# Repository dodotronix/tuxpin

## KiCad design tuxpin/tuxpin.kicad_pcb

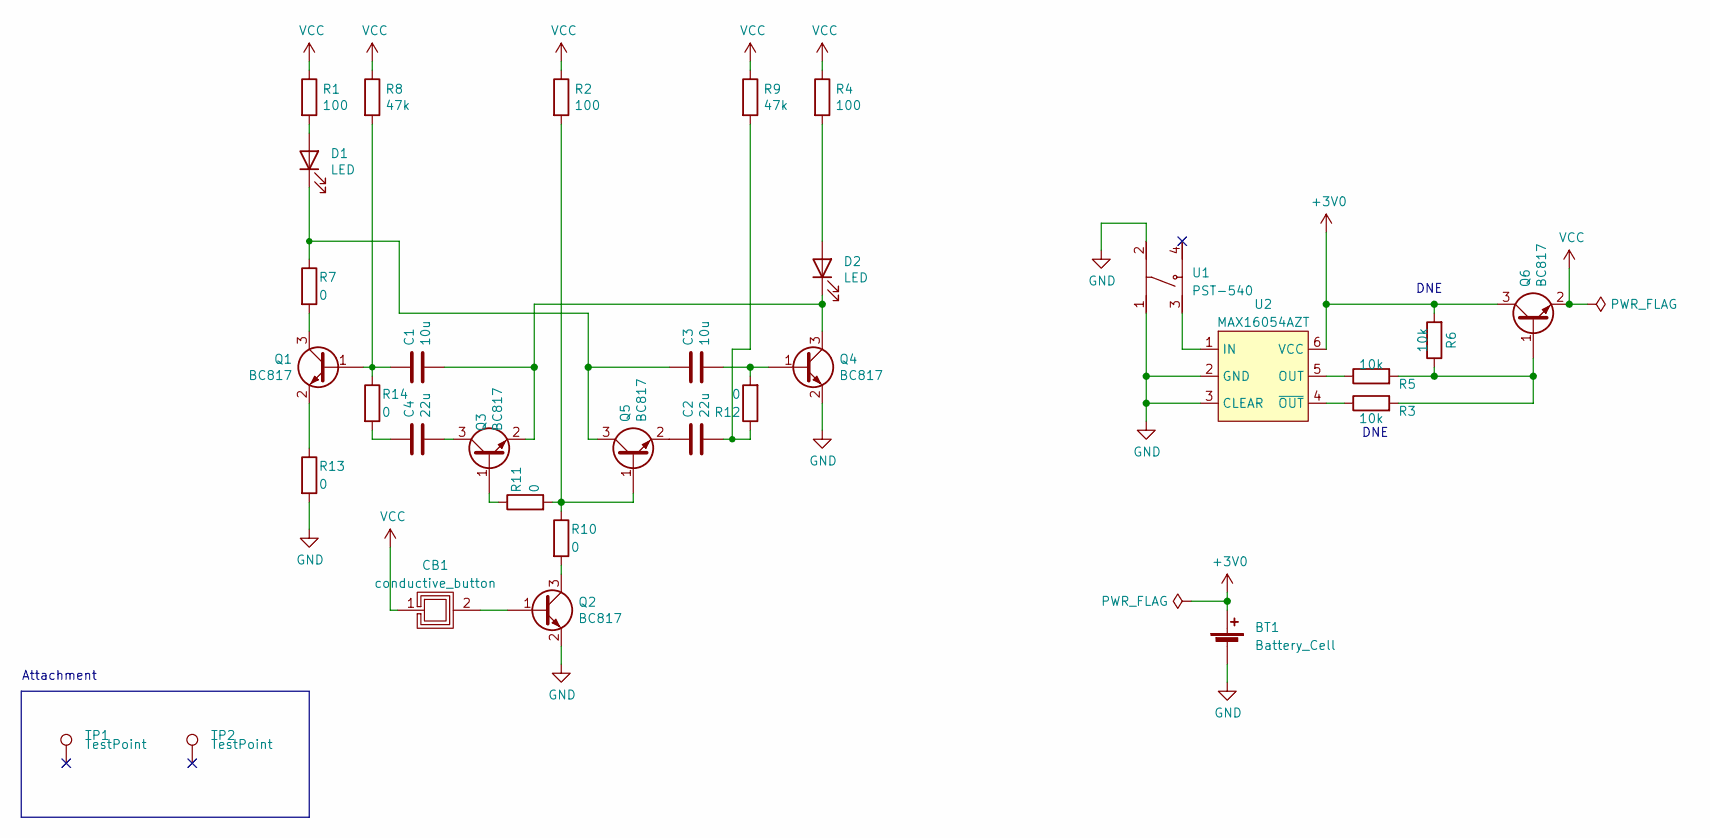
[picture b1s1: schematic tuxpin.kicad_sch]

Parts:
BT1: Battery_Cell; BatteryHolder_Keystone_3000_1x12mm
C1, C3: 10u; C_0603_1608Metric_Pad1.08x0.95mm_HandSolder
C2, C4: 22u; C_0805_2012Metric_Pad1.18x1.45mm_HandSolder
CB1: conductive_button; cat_back
D1, D2: LED; LED_1206_3216Metric_Pad1.42x1.75mm_HandSolder
Q1, Q2, Q3, Q4, Q5, Q6: BC817; SOT-23
R1, R2, R4: 100; R_0603_1608Metric_Pad0.98x0.95mm_HandSolder
R3, R5, R6: 10k; R_0603_1608Metric_Pad0.98x0.95mm_HandSolder
R7, R10, R11, R12, R13, R14: 0; R_0805_2012Metric_Pad1.20x1.40mm_HandSolder
R8, R9: 47k; R_0603_1608Metric_Pad0.98x0.95mm_HandSolder
TP1, TP2: TestPoint; TestPoint_Pad_2.5x2.5mm
U1: PST-540; PTS-540
U2: MAX16054AZT; SOT-23-6_Handsoldering

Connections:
+3V0: BT1.1 (+), Q6.3 (C), R6.2, U2.6 (VCC)
GND: BT1.2 (-), Q2.2 (E), Q4.2 (E), R13.2, U1.1, U1.2, U2.2 (GND), U2.3 (CLEAR)
unnamed: C2.1, R9.2, R12.1
unnamed: C4.1, R14.2
unnamed: D1.2 (A), R1.2
unnamed: C3.2, D1.1 (K), Q5.3 (C), R7.1
unnamed: D2.2 (A), R4.2
unnamed: C1.1, D2.1 (K), Q3.2 (E), Q4.3 (C)
unnamed: C1.2, Q1.1 (B), R8.2, R14.1
unnamed: Q1.3 (C), R7.2
unnamed: Q1.2 (E), R13.1
unnamed: CB1.2, Q2.1 (B)
unnamed: Q2.3 (C), R10.2
unnamed: Q3.1 (B), R11.1
unnamed: C4.2, Q3.3 (C)
unnamed: C3.1, Q4.1 (B), R12.2
unnamed: Q5.1 (B), R2.2, R10.1, R11.2
unnamed: C2.2, Q5.2 (E)
unnamed: Q6.1 (B), R3.2, R5.2, R6.1
unnamed: U1.3, U2.1 (IN)
unnamed: R5.1, U2.5 (OUT)
unnamed: R3.1, U2.4 (~OUT)
VCC: CB1.1, Q6.2 (E), R1.1, R2.1, R4.1, R8.1, R9.1

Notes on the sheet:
DNE
Attachment

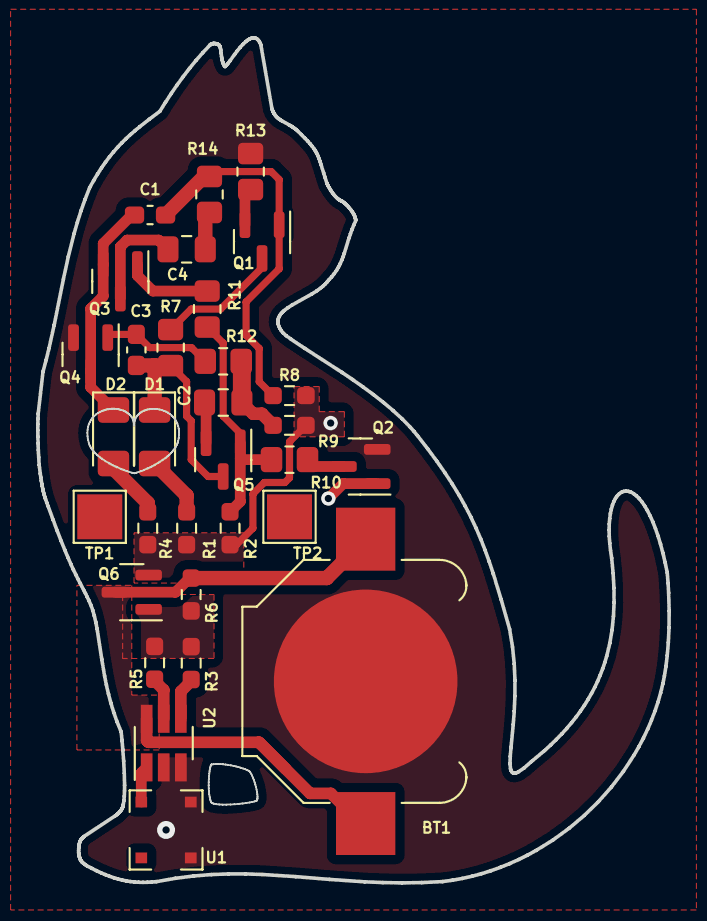
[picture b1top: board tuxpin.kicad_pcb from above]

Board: 2 copper layers, 35.1 x 46.9 mm, 32 parts (1 on the bottom side), 23 nets.

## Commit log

2021-12-23 new blank kicad project
2021-12-23 new gitignore
2021-12-23 new blank readme
2021-12-26 cat silhouette
2021-12-26 not finnished routing
2022-01-05 added conductive button
2022-01-08 first fabrication outputs
2022-01-08 made heart smaller and thinner
2022-01-08 first version of pcb -> ERC doesn't pass
2022-01-11 drc almost without errors - library error battery holder
2022-01-23 fabrication and flatcam outputs for bcnc
2022-01-23 removed redundant cutedges gcodes
2022-01-23 regenerated flatcam for x axis mirroring
2022-01-24 changed size of the cutout in the pcb
2022-02-12 removed old gerbers, and created a updated final pcb
2022-02-13 updated fabrication outputs
2022-02-19 pcb updated fabrication config
2022-03-17 simulation of the flip-flop values
2022-03-17 changed bias point of the resistive button
